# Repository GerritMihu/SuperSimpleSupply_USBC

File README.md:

<h1 align="center">USB-C_Supply_Board</h1>

<p align="center" width="100%">
  
</p>

***

<p align="center">
  
&nbsp; &nbsp; &nbsp; &nbsp;
  
</p>

***

## SPECIFICATIONS

| Parameter | Value | 
| --- | --- |
| Dimensions | 30.5 × 13.0 mm |

***

## DIRECTORY STRUCTURE

    .
    ├─ Computations       # Misc calculations
    ├─ HTML               # HTML files for generated webpage
    ├─ Images             # Pictures and renders
    │
    ├─ kibot_resources    # External resources for KiBot
    │  ├─ colors          # Color theme for KiCad
    │  ├─ fonts           # Fonts used in the project
    │  ├─ scripts         # External scripts used with KiBot
    │  └─ templates       # Templates for KiBot generated reports
    │
    ├─ kibot_yaml         # KiBot YAML config files
    ├─ KiRI               # KiRI (PCB diff viewer) files
    │
    ├─ lib                # KiCad footprint and symbol libraries
    │  ├─ 3d_models       # Component 3D models
    │  ├─ lib_fp          # Footprint libraries
    │  └─ lib_sym         # Symbol libraries
    │
    ├─ Logos              # Logos
    │
    ├─ Manufacturing      # Assembly and fabrication documents
    │  ├─ Assembly        # Assembly documents (BoM, pos, notes)
    │  │
    │  └─ Fabrication     # Fabrication documents (ZIP, notes)
    │     ├─ Drill Tables # CSV drill tables
    │     └─ Gerbers      # Gerbers
    │
    ├─ Report             # Reports for ERC/DRC
    ├─ Schematic          # PDF of schematic
    ├─ Templates          # Title block templates
    ├─ Testing
    │  └─ Testpoints      # Testpoints tables      
    │
    └─ Variants           # Outputs for assembly variants

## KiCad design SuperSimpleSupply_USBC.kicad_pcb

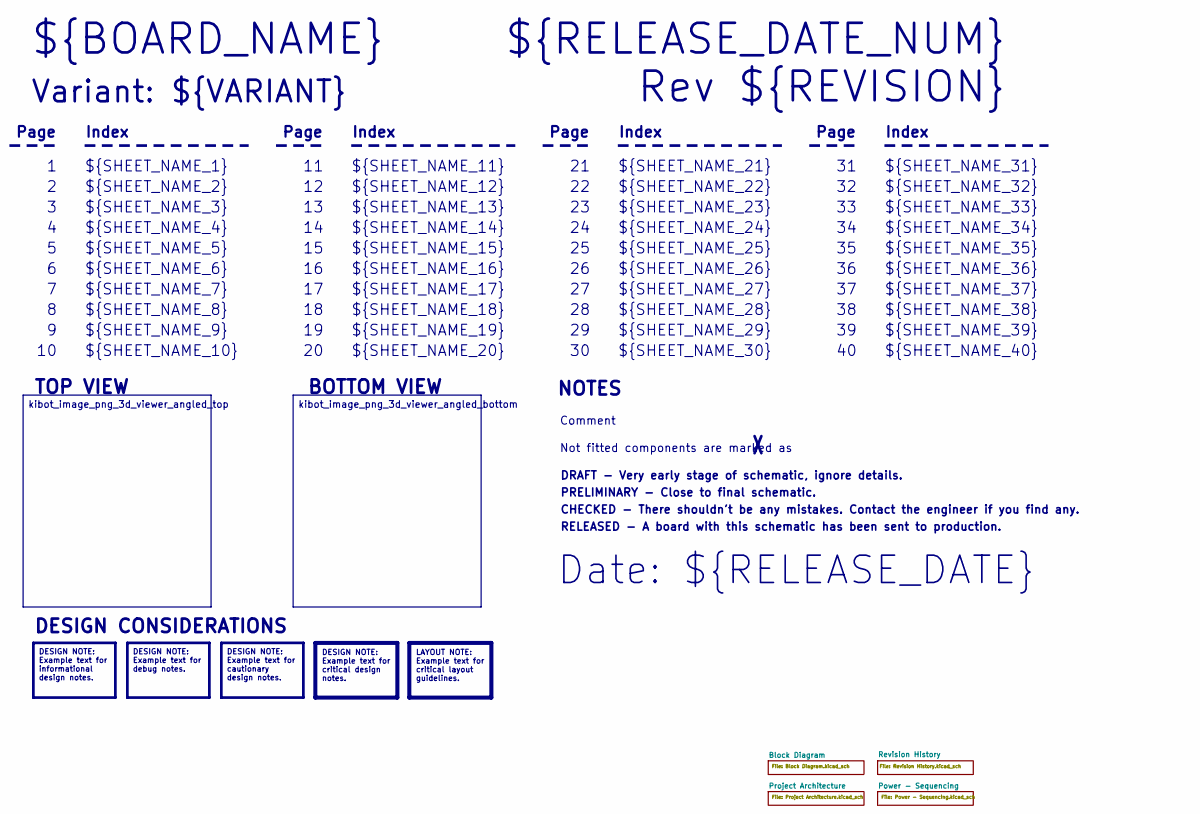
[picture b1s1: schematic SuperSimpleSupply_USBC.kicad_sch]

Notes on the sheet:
Variant: ${VARIANT}
RELEASED - A board with this schematic has been sent to production.
${SHEET_NAME_24}
Index
Page
PRELIMINARY - Close to final schematic.
${SHEET_NAME_22}
DRAFT - Very early stage of schematic, ignore details.
${SHEET_NAME_12}
${SHEET_NAME_8}
${SHEET_NAME_2}
${SHEET_NAME_5}
${SHEET_NAME_20}
${SHEET_NAME_23}
${RELEASE_DATE_NUM}
${SHEET_NAME_35}
Not fitted components are marked as
${SHEET_NAME_11}
${SHEET_NAME_6}
${SHEET_NAME_37}
${SHEET_NAME_26}
${SHEET_NAME_36}
Rev ${REVISION}
${SHEET_NAME_15}
CHECKED - There shouldn't be any mistakes. Contact the engineer if you find any.
BOTTOM VIEW
${SHEET_NAME_14}
${SHEET_NAME_21}
${SHEET_NAME_17}
${SHEET_NAME_18}
Date: ${RELEASE_DATE}
${SHEET_NAME_7}
${SHEET_NAME_31}
${BOARD_NAME}
NOTES
${SHEET_NAME_40}
${SHEET_NAME_39}
${SHEET_NAME_32}
${SHEET_NAME_1}
${SHEET_NAME_9}

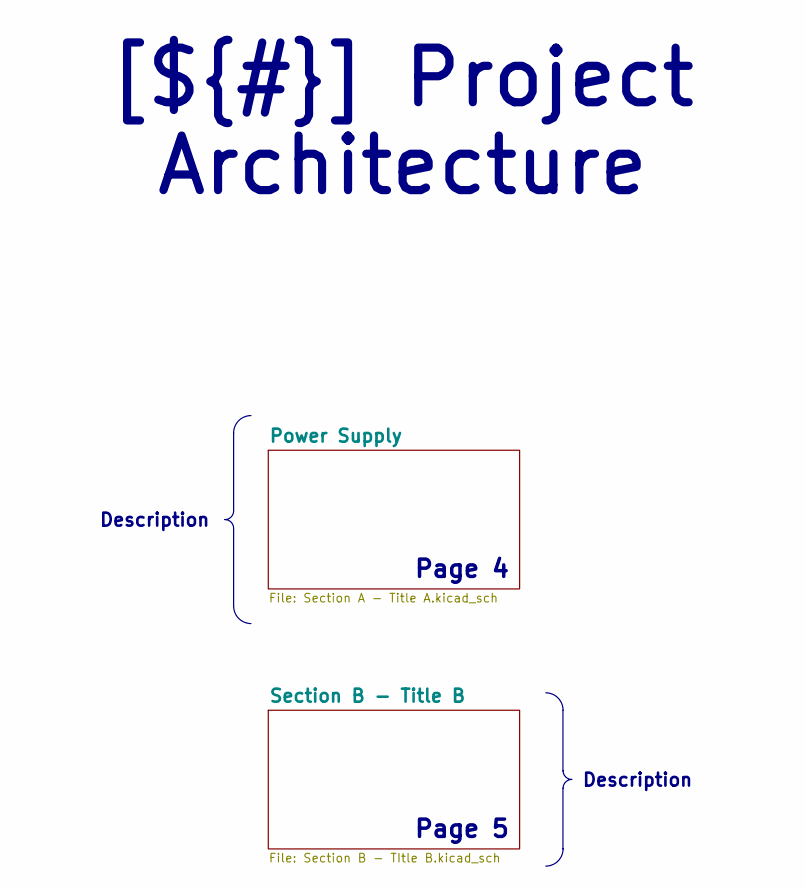
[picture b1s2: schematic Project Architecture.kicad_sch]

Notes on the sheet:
Page 5
Page 4
Description
[${#}] ${TITLE}

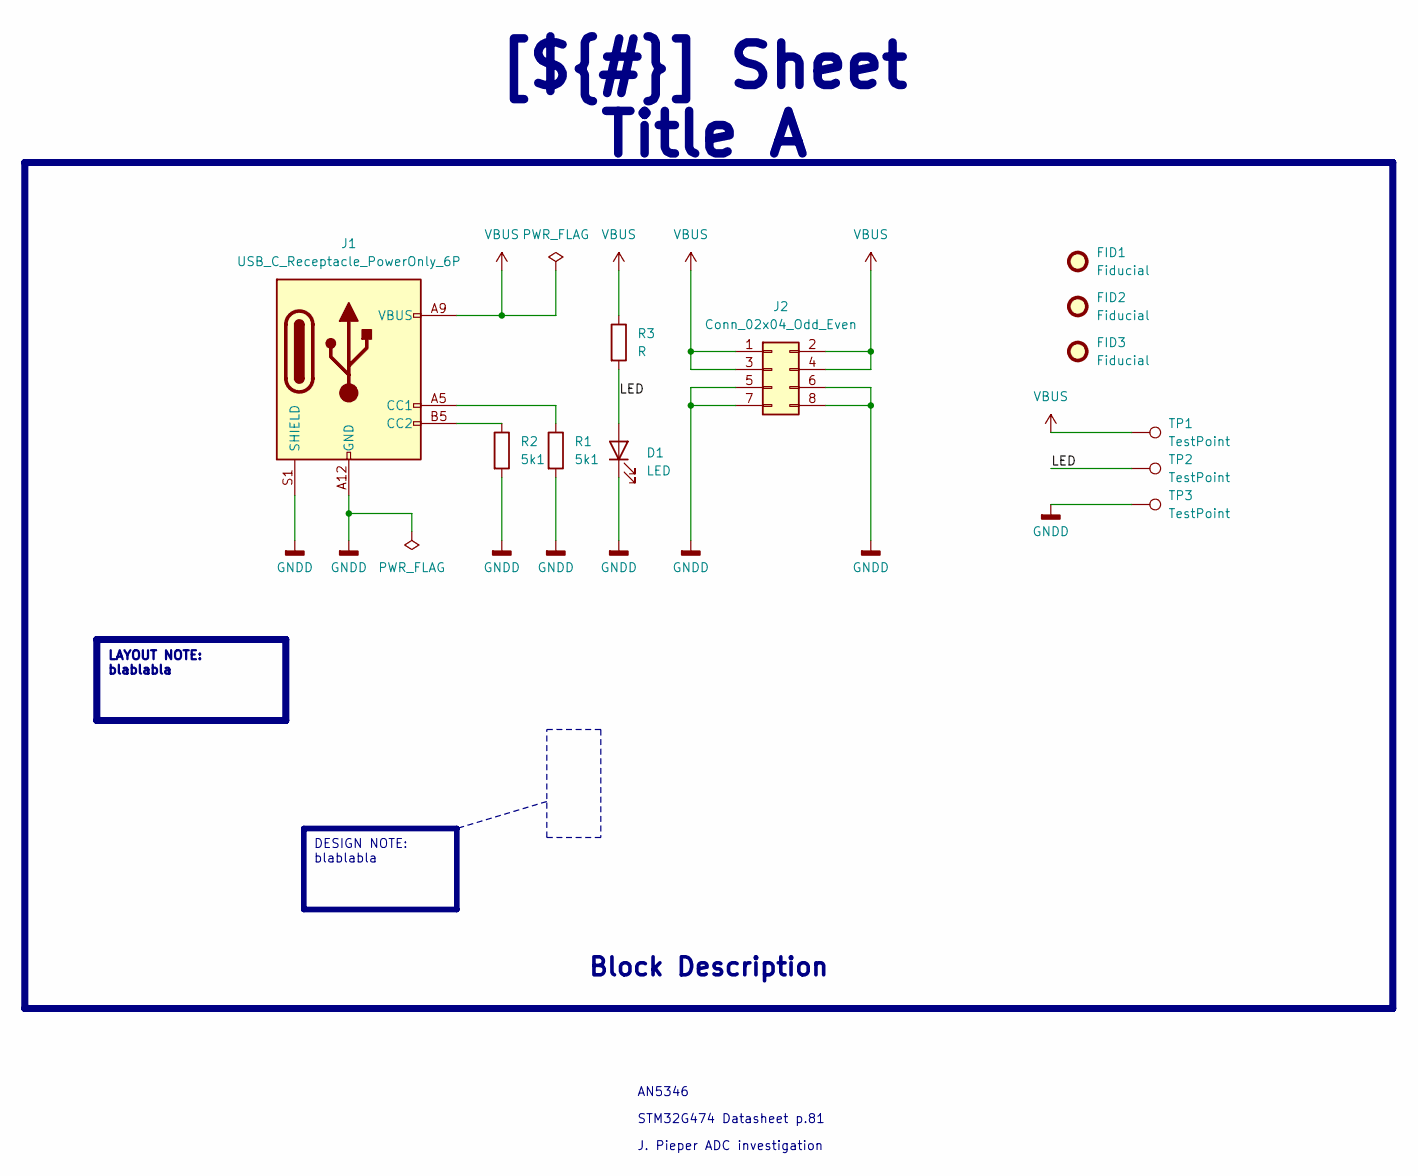
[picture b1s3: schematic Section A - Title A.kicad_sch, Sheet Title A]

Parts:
D1: LED; LED_0402_1005Metric_Pad0.77x0.64mm_HandSolder
FID1, FID2, FID3: Fiducial; Fiducial_1.5mm_Mask3mm
J1: USB_C_Receptacle_PowerOnly_6P; USB_C_Receptacle_GCT_USB4125-xx-x_6P_TopMnt_Horizontal
J2: Conn_02x04_Odd_Even; PinHeader_2x04_P2.54mm_Vertical
R1, R2: 5k1; R_0805_2012Metric_Pad1.20x1.40mm_HandSolder
R3: R; R_0805_2012Metric_Pad1.20x1.40mm_HandSolder
TP1, TP2, TP3: TestPoint; TestPoint_Pad_D1.5mm

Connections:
/Project Architecture/Power Supply/LED: D1.2 (A), R3.2, TP2.1
GNDD: D1.1 (K), J1.A12 (GND), J1.B12 (GND), J1.S1 (SHIELD), J2.5, J2.6, J2.7, J2.8, R1.2, R2.2, TP3.1
unnamed: J1.A5 (CC1), R1.1
unnamed: J1.B5 (CC2), R2.1
VBUS: J1.A9 (VBUS), J1.B9 (VBUS), J2.1, J2.2, J2.3, J2.4, R3.1, TP1.1

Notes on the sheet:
J. Pieper ADC investigation
STM32G474 Datasheet p.81
AN5346
LAYOUT NOTE: blablabla
[${#}] ${TITLE}
Block Description
DESIGN NOTE: blablabla

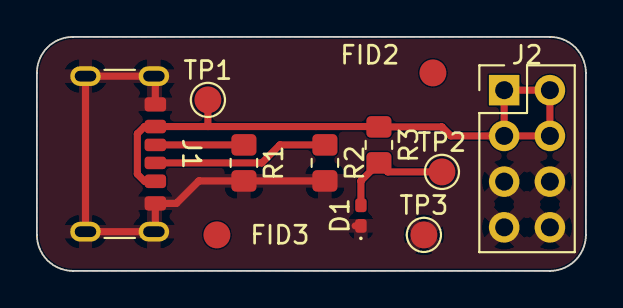
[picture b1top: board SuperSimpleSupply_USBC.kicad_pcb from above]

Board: 2 copper layers, 30.5 x 13.0 mm, 12 parts (1 on the bottom side), 5 nets.

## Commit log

2026-02-17 Update Outputs
2026-02-17 Update project and company metadata in YAML
2026-02-17 Footprints, Testpoints, pwrflag
2026-02-18 [PCB/Sch] Generated PCB
2026-02-18 [PCB] Checked Fiduccials
2026-05-19 created .dxf
